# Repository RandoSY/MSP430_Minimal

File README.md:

# MSP430G2553 20-pin DIP laboratory development board — v1.0

A simple **2-layer, 109 × 71 mm**, mostly through-hole KiCad project inspired by the MSP430 Minimal breakout (not a copy). Designed for **MSP430G2553IN20** in a 20-pin DIP socket. All 20 package pins are present on labeled breakout connectors.

## Files

- `MSP430G2553_LabBoard.kicad_pro`, `.kicad_sch`, `.kicad_pcb`: open the project, schematic, and routed PCB in KiCad 9 (or compatible).
- `UMA_MSP430.kicad_sym`, `UMA_MSP430.pretty/`, `sym-lib-table`, `fp-lib-table`: **project-local custom symbols/footprints**; keep these beside the KiCad files.
- `PCB_preview.png`: current copper-layer overview (red: front; blue: back).
- `PCB_back_silkscreen_preview.png`: mirrored back-side silkscreen and pad-opening preview.
- `ROUTING_WORKFLOW.md`: Freerouting version, settings, and repeatable DSN/SES workflow.
- `PCB_DRC.json`: latest KiCad PCB DRC report.
- `BOM.csv`: Bill of Materials.
- `NETLIST.csv`: complete electrical cross-check net/pin list.
- `ROUTING.json` and `GEOMETRY_CHECK.json`: historical routing and approximate copper-check data from the earlier layout; they do not describe the current PCB.

## Connectors

| Header | Pin 1 | Pin 2 | Pin 3 | Pin 4 |
|---|---|---|---|---|
| J3 — 3.3V UART | +3V3 | GND | MCU TX (P1.2) | MCU RX (P1.1) |
| J4 — Spy-Bi-Wire | +3V3 | GND | RST/SBWTDIO | TEST/SBWTCK |
| J5 — I²C | +3V3 | GND | SCL (P1.6) | SDA (P1.7) |

**J1** pins 1–10 = MCU physical DIP pins 1–10 (in order); **J2** pins 1–10 = DIP pins 20–11 (top to bottom). J1/J2 expose all I/O, supply and debug pins, including multiplexed P2.6/P2.7. See `NETLIST.csv` for exact labels.

## Features & wiring

- **U1:** 20-pin MSP430G2553IN20 (3.3 V regulated supply; no on-board regulator).
- **Power:** C2 100 nF ceramic and C3 10 µF bulk capacitor across supply; C3 pin 1 is positive (+3V3), pin 2 is ground; check actual body size and polarity against footprint.
- **SBW:** R1 47 kΩ pull-up to RST, C1 1 nF to ground and reset switch SW3. Do not increase SBW capacitance without verifying debugger compatibility.
- **I²C:** R2/R3 each 4.7 kΩ to +3V3 on SCL/SDA. These are fixed pull-ups: omit resistors if the external bus already has sufficient pull-up strength.
- **LEDs:** D1 green on P1.0 and D2 amber on P1.4; each fed by 1 kΩ current-limiting resistor; firmware drives the GPIO high to illuminate.
- **User switches:** SW1 -> P2.0/GND, SW2 -> P2.1/GND. Enable MCU internal input pull-ups in firmware. SW3 resets MCU.
- **Piezo:** BZ1 12 mm passive piezo footprint, two pins 7.62 mm apart, powered through NPN Q1 (2N3904 E/B/C). P2.3 drives Q1 base through R6=1k; R7=100k holds transistor off; firmware PWM/TIMER output allows tones. Confirm piezo terminal pitch and TO-92 E/B/C lead ordering for your actual parts.
- **Slide control:** RV1 10 kΩ Bourns **PTA3043-2010CPB103** linear slide potentiometer, 30 mm stroke, 45 mm body. End terminals to supply/ground, wiper on P1.3/A3. C4 10 nF filters ADC input. The project includes four proposed 1.8-mm clearance holes for mounting lugs; **test the physical hole pattern against the selected manufacturer's mechanical drawing before fabrication**.
- MCU uses its internal oscillator; P2.6/P2.7 are available as GPIO rather than populated with a 32-kHz crystal.

## Power and safety

**Connect only regulated 3.3 V** to J3 or J4. Neither the chip nor the UART header is 5 V tolerant. This is a **TTL-level UART header, not a DB9/±12 V RS-232 port**. With multiple programmers/adapters, power from only one source or isolate VCC appropriately. No USB, voltage regulator, or reverse-polarity protection is provided.

## Before you order from DirtyPCBs

1. Open the `.kicad_pro` project in KiCad and confirm the schematic parses and all custom symbol libraries resolve.
2. Run **Tools → Electrical Rules Checker (ERC)** in Schematic Editor. The symbol/footprint libraries were written programmatically, not native KiCad-validated.
3. In PCB Editor, refill any copper zones (none needed here); run **Inspect → Design Rules Checker (DRC)** with your manufacturer's rules; fix any flags. The latest KiCad DRC reported zero violations and zero unconnected items under the current project rules. Confirm the rules match your manufacturer, and rerun the check after edits.
4. Verify the 6×6 mm tactile switch footprint, transistor TO-92 orientation, 12 mm piezo pin spacing, 10 µF capacitor clearance, and especially **Bourns slide pot** lug hole placement against parts in hand.
5. From PCB Editor choose **File → Fabrication Outputs → Gerbers** and **Drill Files**, generate standard F.Cu/B.Cu/F.Mask/B.Mask/F.SilkS/Edge.Cuts and Excellon drills, then use KiCad Gerber Viewer to inspect.
6. Zip the Gerber/Excellon production outputs (not the source project) and submit the ZIP to https://dirtypcbs.com/store/pcbs. Specify **2 copper layers**, **1.6-mm FR4**, and actual **109×71 mm** board dimensions; verify current service limits and capability first.

**Status: routed prototype draft; run schematic ERC, verify footprint fit, and export and inspect fabrication Gerbers before ordering.** Do not submit this source ZIP as a fabrication-ready Gerber archive.

## Authoritative references

- TI MSP430G2x53 datasheet: https://www.ti.com/lit/ds/symlink/msp430g2553.pdf
- TI MSP430 Hardware Tools, SBW guidance: https://www.ti.com/lit/ug/slau278/slau278.pdf
- Bourns PTA slide potentiometer mechanical drawing: https://www.bourns.com/docs/product-datasheets/pta.pdf
- Inspiration: https://hackaday.io/project/3173-msp430-minimal

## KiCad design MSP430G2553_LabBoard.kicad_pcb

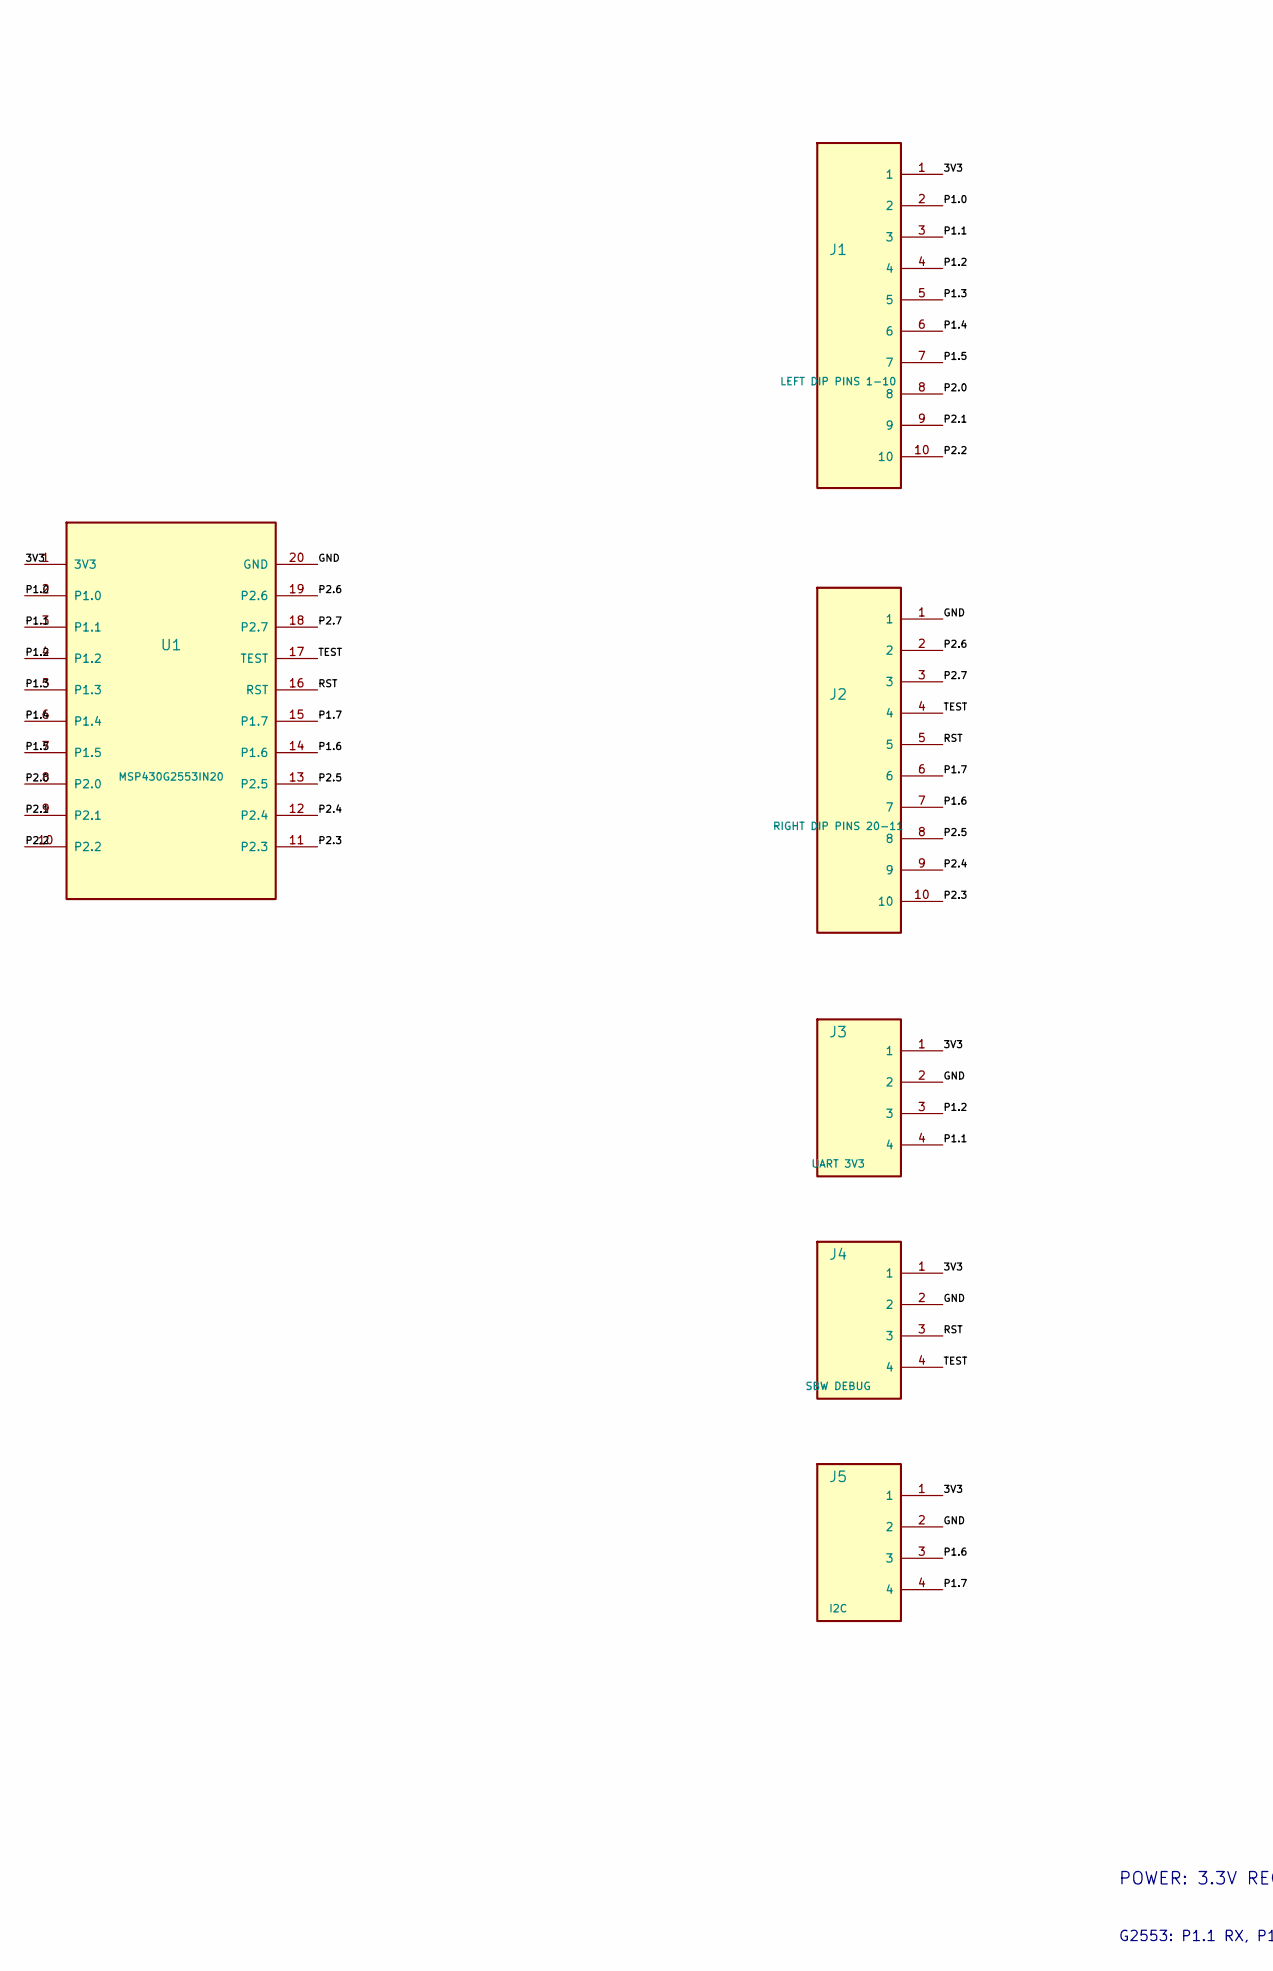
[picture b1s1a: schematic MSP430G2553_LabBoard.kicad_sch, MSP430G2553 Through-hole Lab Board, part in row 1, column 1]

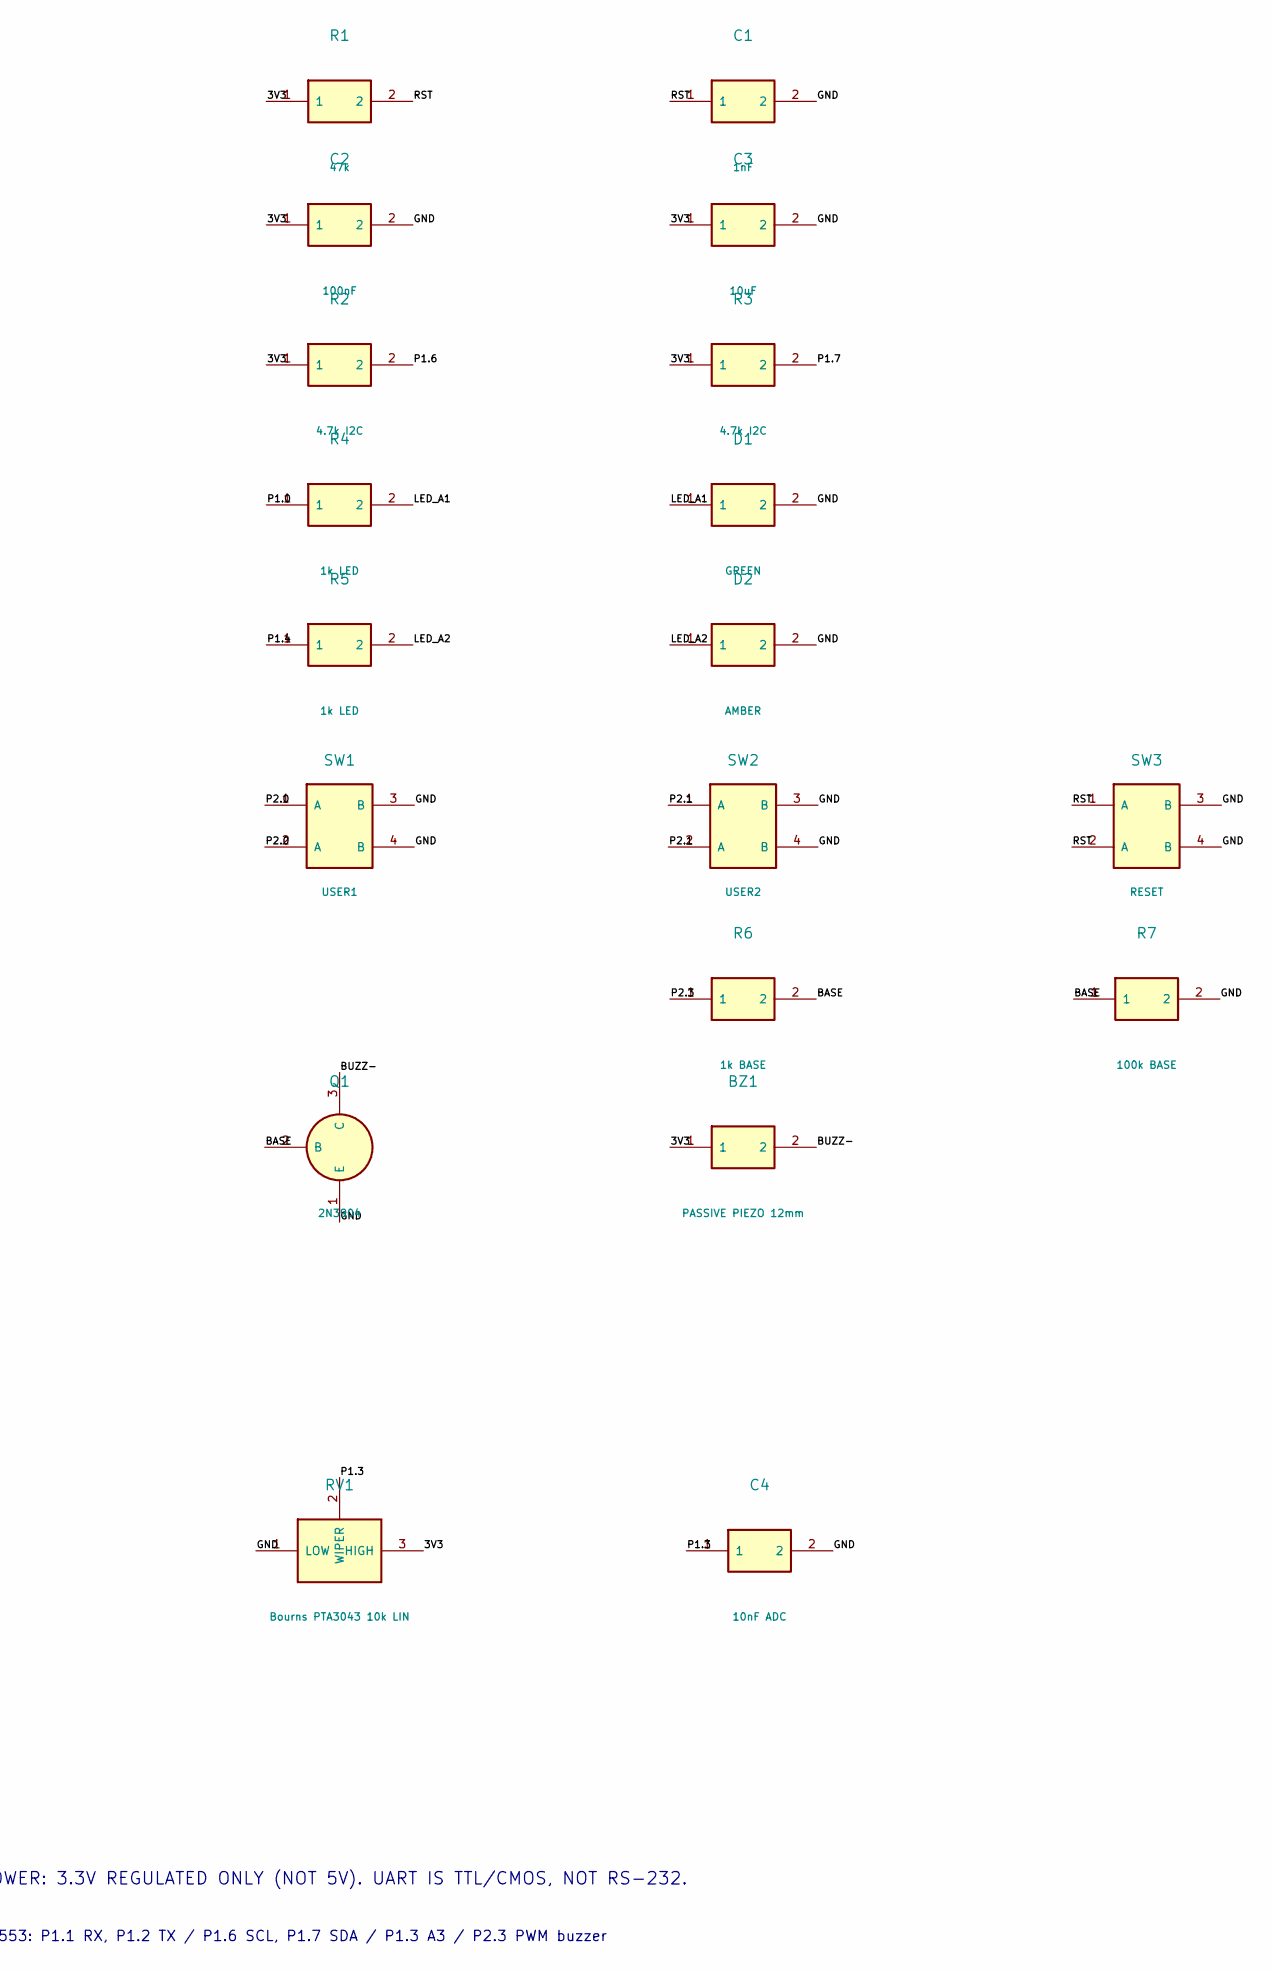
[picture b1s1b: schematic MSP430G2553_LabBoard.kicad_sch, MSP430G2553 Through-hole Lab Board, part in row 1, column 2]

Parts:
BZ1: PASSIVE PIEZO 12mm; PIEZO
C1: 1nF; C5
C2: 100nF; C5
C3: 10uF; C5
C4: 10nF ADC; C5
D1: GREEN; LED5
D2: AMBER; LED5
J1: LEFT DIP PINS 1-10; HDR10
J2: RIGHT DIP PINS 20-11; HDR10
J3: UART 3V3; HDR4H
J4: SBW DEBUG; HDR4H
J5: I2C; HDR4H
Q1: 2N3904; NPN
R1: 47k; R7
R2, R3: 4.7k I2C; R7
R4, R5: 1k LED; R7
R6: 1k BASE; R7
R7: 100k BASE; R7
RV1: Bourns PTA3043 10k LIN; SLIDER
SW1: USER1; TACT4
SW2: USER2; TACT4
SW3: RESET; TACT4
U1: MSP430G2553IN20; DIP20

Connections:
3V3: BZ1.1, C2.1, C3.1, J1.1, J3.1, J4.1, J5.1, R1.1, R2.1, R3.1, RV1.3 (HIGH), U1.1 (3V3)
BASE: Q1.2 (B), R6.2, R7.1
BUZZ-: BZ1.2, Q1.3 (C)
GND: C1.2, C2.2, C3.2, C4.2, D1.2, D2.2, J2.1, J3.2, J4.2, J5.2, Q1.1 (E), R7.2, RV1.1 (LOW), SW1.3 (B), SW1.4 (B), SW2.3 (B), SW2.4 (B), SW3.3 (B), SW3.4 (B), U1.20 (GND)
LED_A1: D1.1, R4.2
LED_A2: D2.1, R5.2
P1.0: J1.2, R4.1, U1.2 (P1.0)
P1.1: J1.3, J3.4, U1.3 (P1.1)
P1.2: J1.4, J3.3, U1.4 (P1.2)
P1.3: C4.1, J1.5, RV1.2 (WIPER), U1.5 (P1.3)
P1.4: J1.6, R5.1, U1.6 (P1.4)
P1.5: J1.7, U1.7 (P1.5)
P1.6: J2.7, J5.3, R2.2, U1.14 (P1.6)
P1.7: J2.6, J5.4, R3.2, U1.15 (P1.7)
P2.0: J1.8, SW1.1 (A), SW1.2 (A), U1.8 (P2.0)
P2.1: J1.9, SW2.1 (A), SW2.2 (A), U1.9 (P2.1)
P2.2: J1.10, U1.10 (P2.2)
P2.3: J2.10, R6.1, U1.11 (P2.3)
P2.4: J2.9, U1.12 (P2.4)
P2.5: J2.8, U1.13 (P2.5)
P2.6: J2.2, U1.19 (P2.6)
P2.7: J2.3, U1.18 (P2.7)
RST: C1.1, J2.5, J4.3, R1.2, SW3.1 (A), SW3.2 (A), U1.16 (RST)
TEST: J2.4, J4.4, U1.17 (TEST)

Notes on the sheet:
POWER: 3.3V REGULATED ONLY (NOT 5V). UART IS TTL/CMOS, NOT RS-232.
G2553: P1.1 RX, P1.2 TX / P1.6 SCL, P1.7 SDA / P1.3 A3 / P2.3 PWM buzzer

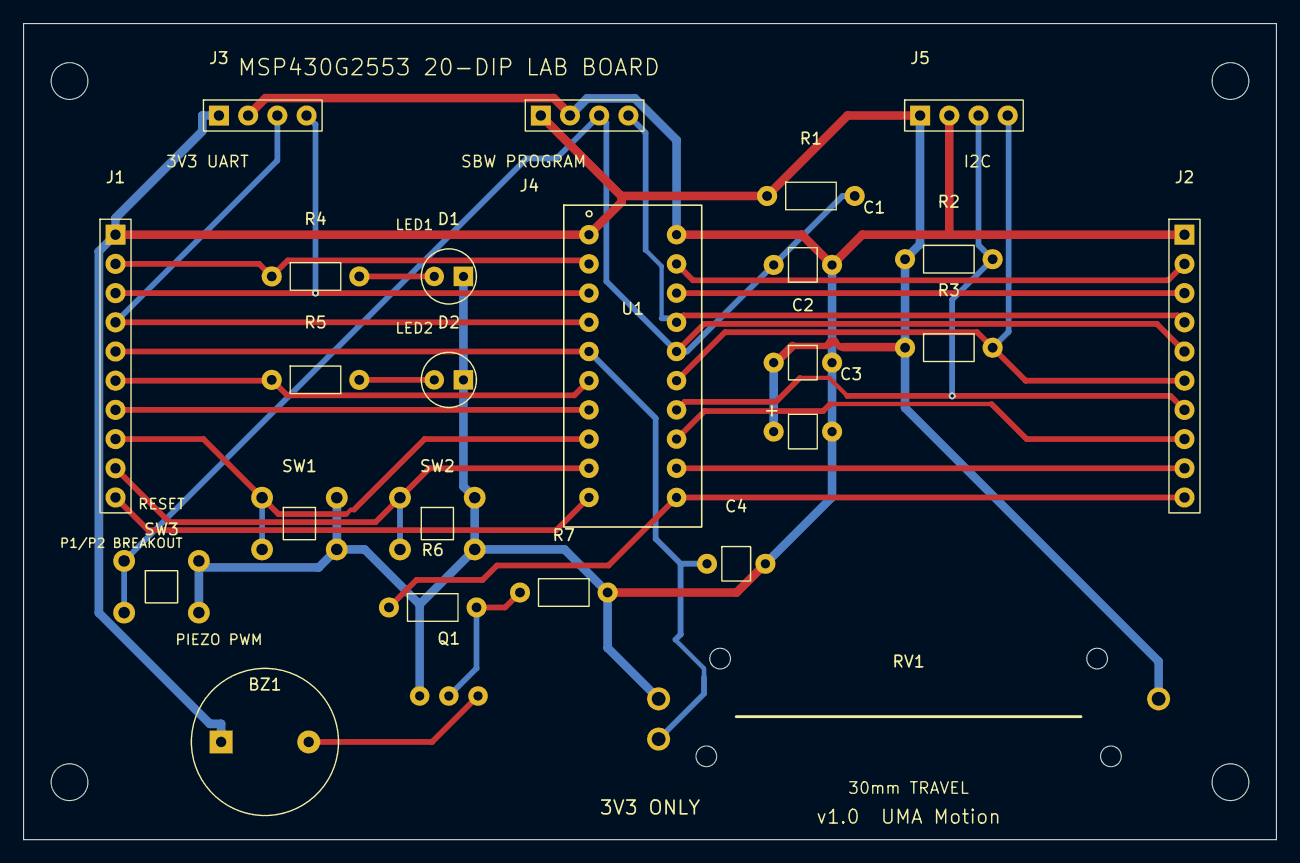
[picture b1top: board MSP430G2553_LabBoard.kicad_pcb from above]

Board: 2 copper layers, 109.0 x 71.0 mm, 29 parts (0 on the bottom side), 24 nets.

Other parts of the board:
MH1, MH2, MH3, MH4: MOUNT
